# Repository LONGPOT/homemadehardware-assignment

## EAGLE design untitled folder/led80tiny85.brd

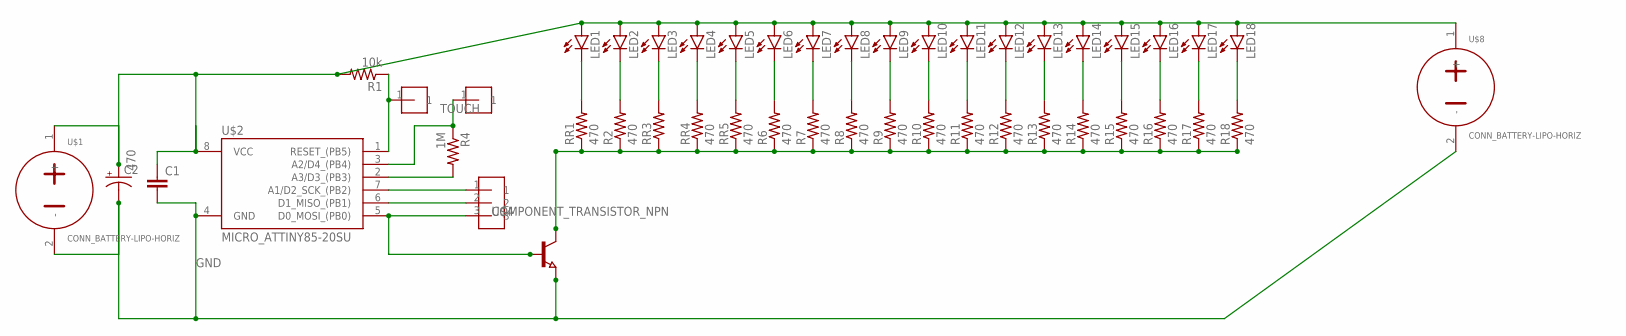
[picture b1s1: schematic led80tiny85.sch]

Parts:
C1: COMPONENT_CAP-0805; 0805
C2: COMPONENT_CAP_POL-8MM; CAP_RADIAL_CAN_6.3MM
LED1, LED2, LED3, LED4, LED5, LED6, LED7, LED8, LED9, LED10, LED11, LED12, LED13, LED14, LED15, LED16, LED17, LED18: LED-0805; CHIP-LED0805
R1: 10k; 0805
R2, R6, R7, R8, R9, R10, R11, R12, R13, R14, R15, R16, R17, R18: 470; 0805
R4: 1M; 0805
RR1, RR3, RR4, RR5: 470; 0805
U$1, U$8: CONN_BATTERY-LIPO-HORIZ; JST-PH-2-SMT-RA
U$2: MICRO_ATTINY85-20SU; SOIC8
U$4: COMPONENT_TRANSISTOR_NPN; SOT23
U$5, U$6: HEADER-1-TESTPOINT; TESTPOINT-1
U$7: HEADER-3-TESTPOINT; TESTPOINT-3

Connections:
GND: C1.2, C2.-, U$1.2 (-), U$2.4 (GND), U$4.2 (E), U$8.2 (-)
unnamed: R1.1, U$2.1 (RESET_(PB5)), U$6.1
unnamed: C1.1, C2.+, LED1.A, LED2.A, LED3.A, LED4.A, LED5.A, LED6.A, LED7.A, LED8.A, LED9.A, LED10.A, LED11.A, LED12.A, LED13.A, LED14.A, LED15.A, LED16.A, LED17.A, LED18.A, R1.2, U$1.1 (+), U$2.8 (VCC), U$8.1 (+)
unnamed: U$2.5 (D0_MOSI_(PB0)), U$4.1 (B), U$7.3
unnamed: R2.1, R6.1, R7.1, R8.1, R9.1, R10.1, R11.1, R12.1, R13.1, R14.1, R15.1, R16.1, R17.1, R18.1, RR1.1, RR3.1, RR4.1, RR5.1, U$4.3 (C)
unnamed: R4.2, U$2.2 (A3/D3_(PB3))
unnamed: U$2.7 (A1/D2_SCK_(PB2)), U$7.1
unnamed: U$2.6 (D1_MISO_(PB1)), U$7.2
unnamed: LED1.C, RR1.2
unnamed: LED2.C, R2.2
unnamed: LED3.C, RR3.2
unnamed: LED4.C, RR4.2
unnamed: LED5.C, RR5.2
unnamed: LED6.C, R6.2
unnamed: LED7.C, R7.2
unnamed: LED8.C, R8.2
unnamed: LED9.C, R9.2
unnamed: LED10.C, R10.2
unnamed: LED11.C, R11.2
unnamed: LED12.C, R12.2
unnamed: LED13.C, R13.2
unnamed: LED14.C, R14.2
unnamed: LED15.C, R15.2
unnamed: LED16.C, R16.2
unnamed: LED17.C, R17.2
unnamed: LED18.C, R18.2
TOUCH: R4.1, U$2.3 (A2/D4_(PB4)), U$5.1

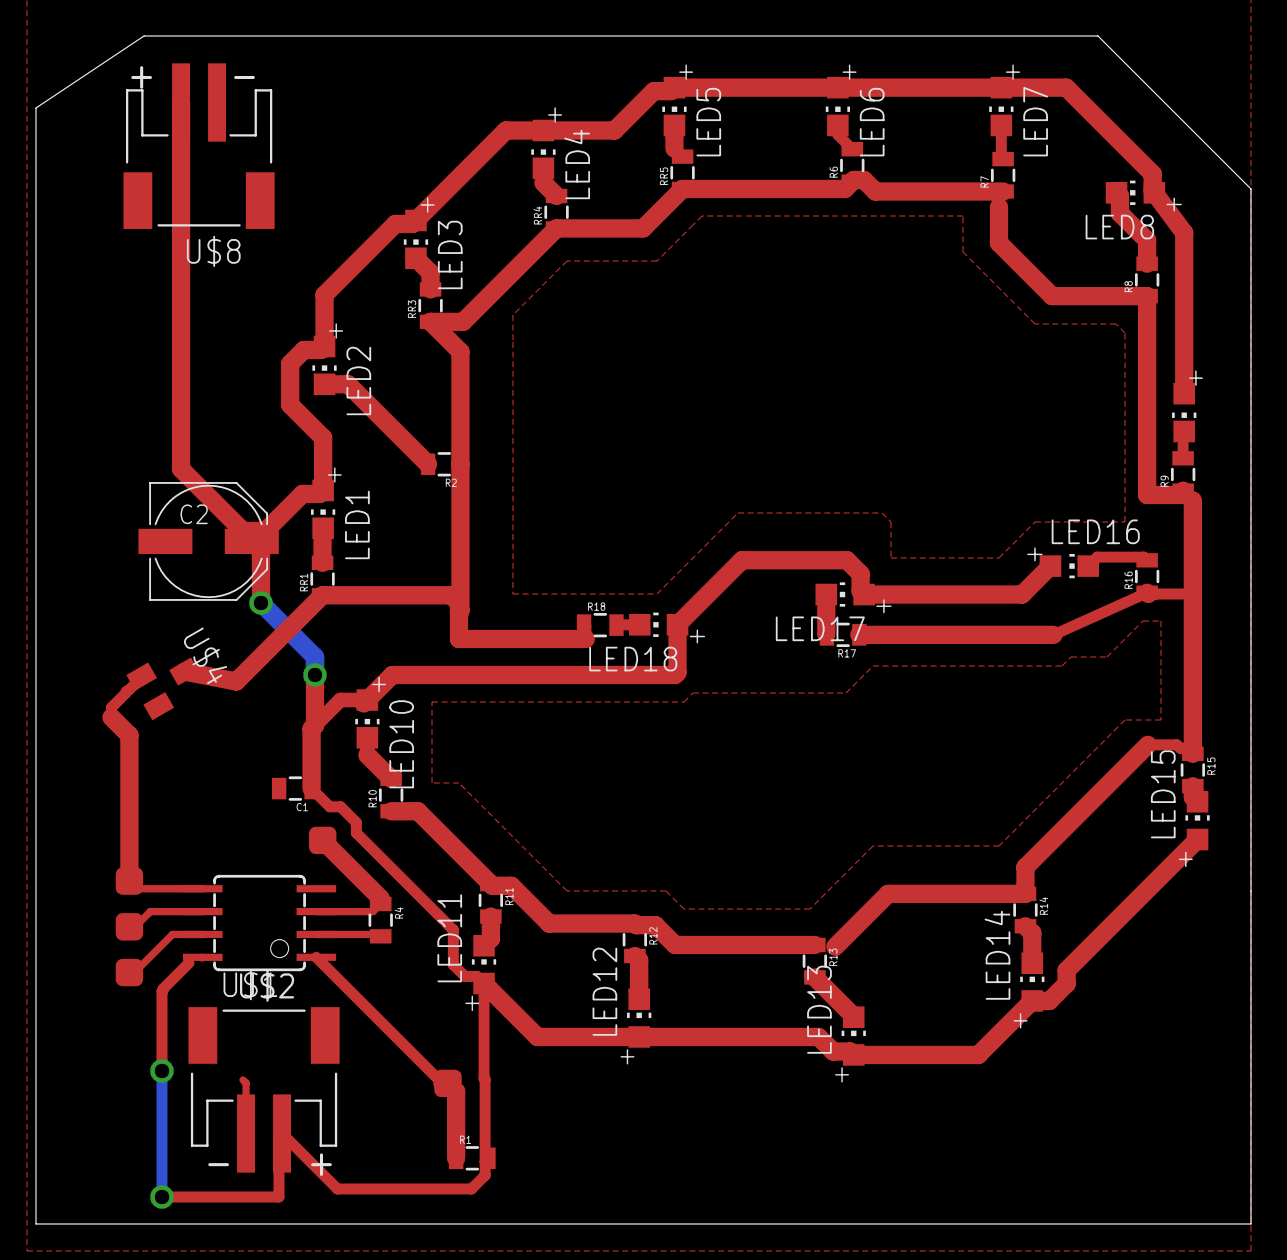
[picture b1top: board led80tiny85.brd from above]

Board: 2 copper layers, 67.5 x 66.0 mm, 47 parts (0 on the bottom side), 27 nets.

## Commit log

2020-02-23 my character e
